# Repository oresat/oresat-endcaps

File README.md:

# "End Cap" PCBs for OreSat

These are the "end cap" PCBs that attach to the +Z and -Z ends of the satellites. Mostly these are to protect the end cards from "space", as well as to hold the magnetometers (two per end cap) as far as away from ferrous stuff as possible. It's also a good place for backup antennas, specifically patch antennas (S band and GPS L1).

## Features

- Cutouts for deployable antennas
- Double magnetometers.
- Single vertical 10mm tall 1.27 mm connector that plugs into the "end card" card.
    - On the End Cap:  Harwin M55-6001242R 12 pin female vertical connector 
    - On the End Card below: Harwin M55-7011242R 12 pin male vertical connector
- No available RF connectors.

## LICENSE

Copyright the Portland State Aerospace Society, 2024.

This source describes Open Hardware that is licensed under CERN-OHL-S v2, or any later version.

You may redistribute and modify this source and make products using it under the terms of the CERN-OHL-S v2 (https://ohwr.org/cern_ohl_s_v2.txt).

This source is distributed WITHOUT ANY EXPRESS OR IMPLIED WARRANTY, INCLUDING OF MERCHANTABILITY, SATISFACTORY QUALITY AND FITNESS FOR A PARTICULAR PURPOSE. Please see the CERN-OHL-S v2 for applicable conditions.

Source location: <https://github.com/oresat/>

As per CERN-OHL-S v2 section 4, should You produce hardware based on this source, You must where practicable maintain the Source Location visible on the external case of the Gizmo or other products you make using this source.

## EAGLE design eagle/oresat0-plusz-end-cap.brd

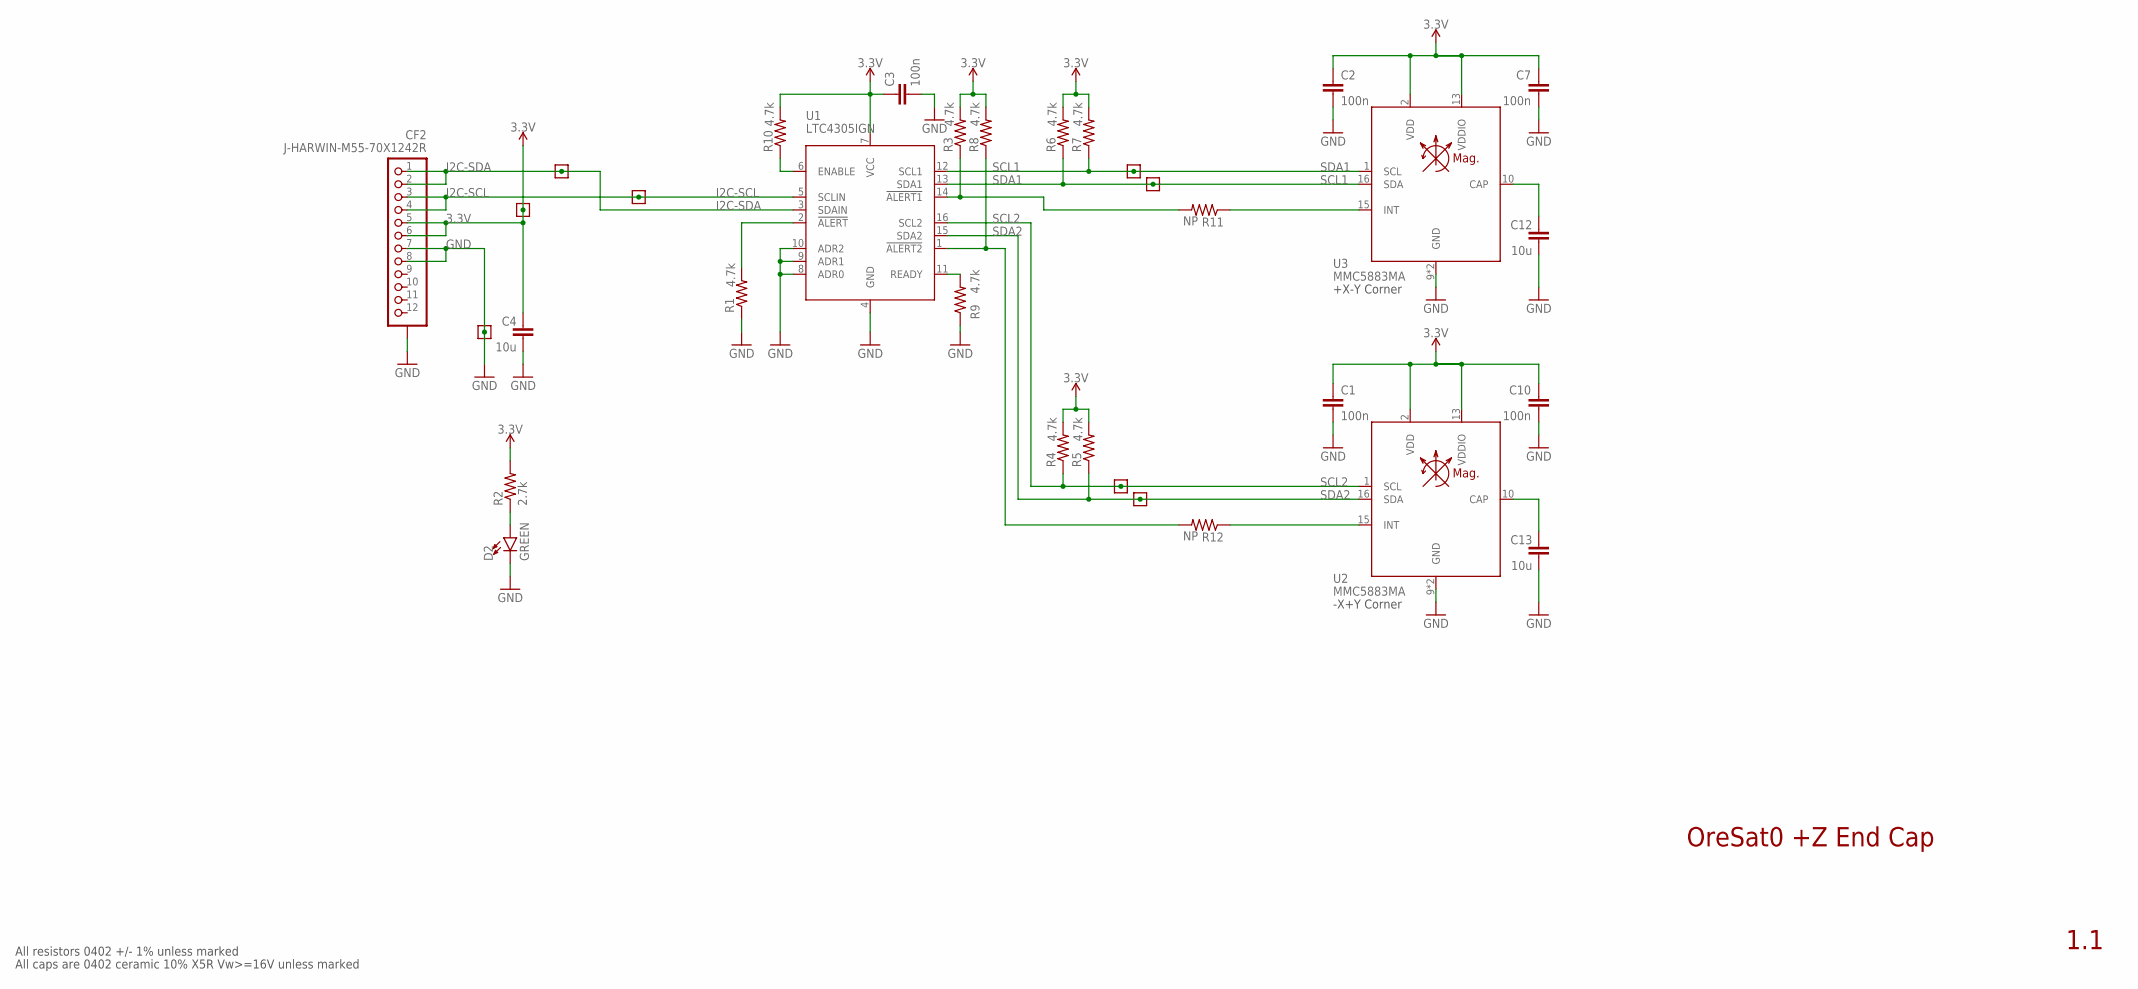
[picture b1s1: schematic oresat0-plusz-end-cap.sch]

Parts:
C1, C2, C3, C7, C10: 100n; .0603-B-NOSILK; MPN CL10B104KB8NNNL
C4, C12, C13: 10u; .0603-B-NOSILK; MPN GRM188D71A106KA73D
CF2: J-HARWIN-M55-70X1242R; HARWIN-M55-70X1242R; MPN M55-7011242R
D2: GREEN; LED-0603; MPN SML-E12M8WT86
R1, R3, R4, R5, R6, R7, R8, R9, R10: 4.7k; .0603-B-NOSILK; MPN CRGCQ0603F4K7
R2: 2.7k; .0603-B-NOSILK; MPN CRGCQ0603F2K7
R11, R12: NP; .0603-B-NOSILK
TP1, TP2, TP3, TP4, TP5, TP6, TP7, TP8: TEST-POINT-LARGE-SQUARE; 1X01
U1: LTC4305IGN; 16-SSOP; MPN LTC4305IGN#PBF
U2, U3: MMC5883MA; LGA-16(3X3); MPN MMC5883MA

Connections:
3.3V: C1.1, C2.1, C3.1, C4.1, C7.1, C10.1, CF2.5, CF2.6, R2.2, R3.2, R4.2, R5.2, R6.2, R7.2, R8.2, R10.2, TP7.1, U1.7 (VCC), U2.2 (VDD), U2.13 (VDDIO), U3.2 (VDD), U3.13 (VDDIO)
GND: C1.2, C2.2, C3.2, C4.2, C7.2, C10.2, C12.2, C13.2, CF2.7, CF2.8, CF2.P$1 (SHIELDS), CF2.P$2 (SHIELDS), CF2.P$3 (SHIELDS), CF2.P$4 (SHIELDS), D2.C, R1.1, R9.1, TP8.1, U1.4 (GND), U1.8 (ADR0), U1.9 (ADR1), U1.10 (ADR2), U2.9 (GND), U2.11 (GND), U3.9 (GND), U3.11 (GND)
I2C-SCL: CF2.3, CF2.4, TP3.1, U1.5 (SCLIN)
I2C-SDA: CF2.1, CF2.2, TP6.1, U1.3 (SDAIN)
unnamed: R9.2, U1.11 (READY)
unnamed: C12.1, U3.10 (CAP)
unnamed: R1.2, U1.2 (!ALERT)
unnamed: R3.1, R11.2, U1.14 (!ALERT1)
unnamed: C13.1, U2.10 (CAP)
unnamed: R8.1, R12.2, U1.1 (!ALERT2)
unnamed: R11.1, U3.15 (INT)
unnamed: R10.1, U1.6 (ENABLE)
unnamed: R12.1, U2.15 (INT)
unnamed: D2.A, R2.1
SCL1: R7.1, TP1.1, U1.12 (SCL1), U3.1 (SCL)
SCL2: R4.1, TP4.1, U1.16 (SCL2), U2.1 (SCL)
SDA1: R6.1, TP2.1, U1.13 (SDA1), U3.16 (SDA)
SDA2: R5.1, TP5.1, U1.15 (SDA2), U2.16 (SDA)

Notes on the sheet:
OreSat0 +Z End Cap
1.1
All resistors 0402 +/- 1% unless marked
All caps are 0402 ceramic 10% X5R Vw>=16V unless marked
-X+Y Corner
+X-Y Corner

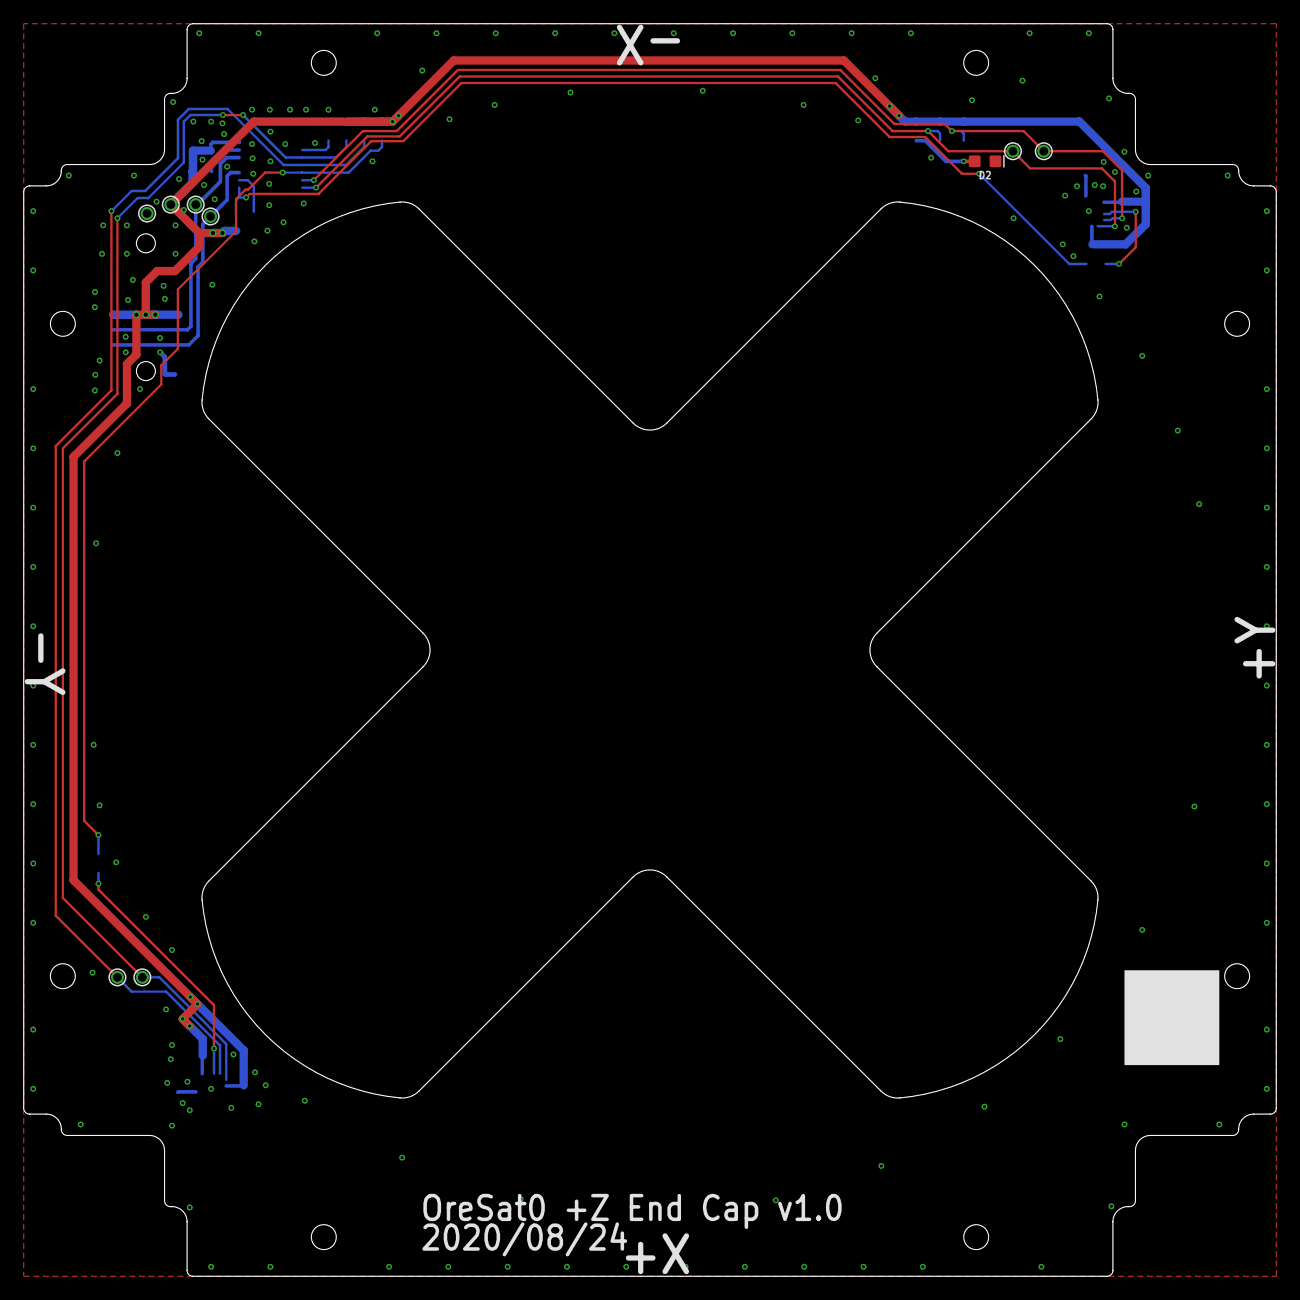
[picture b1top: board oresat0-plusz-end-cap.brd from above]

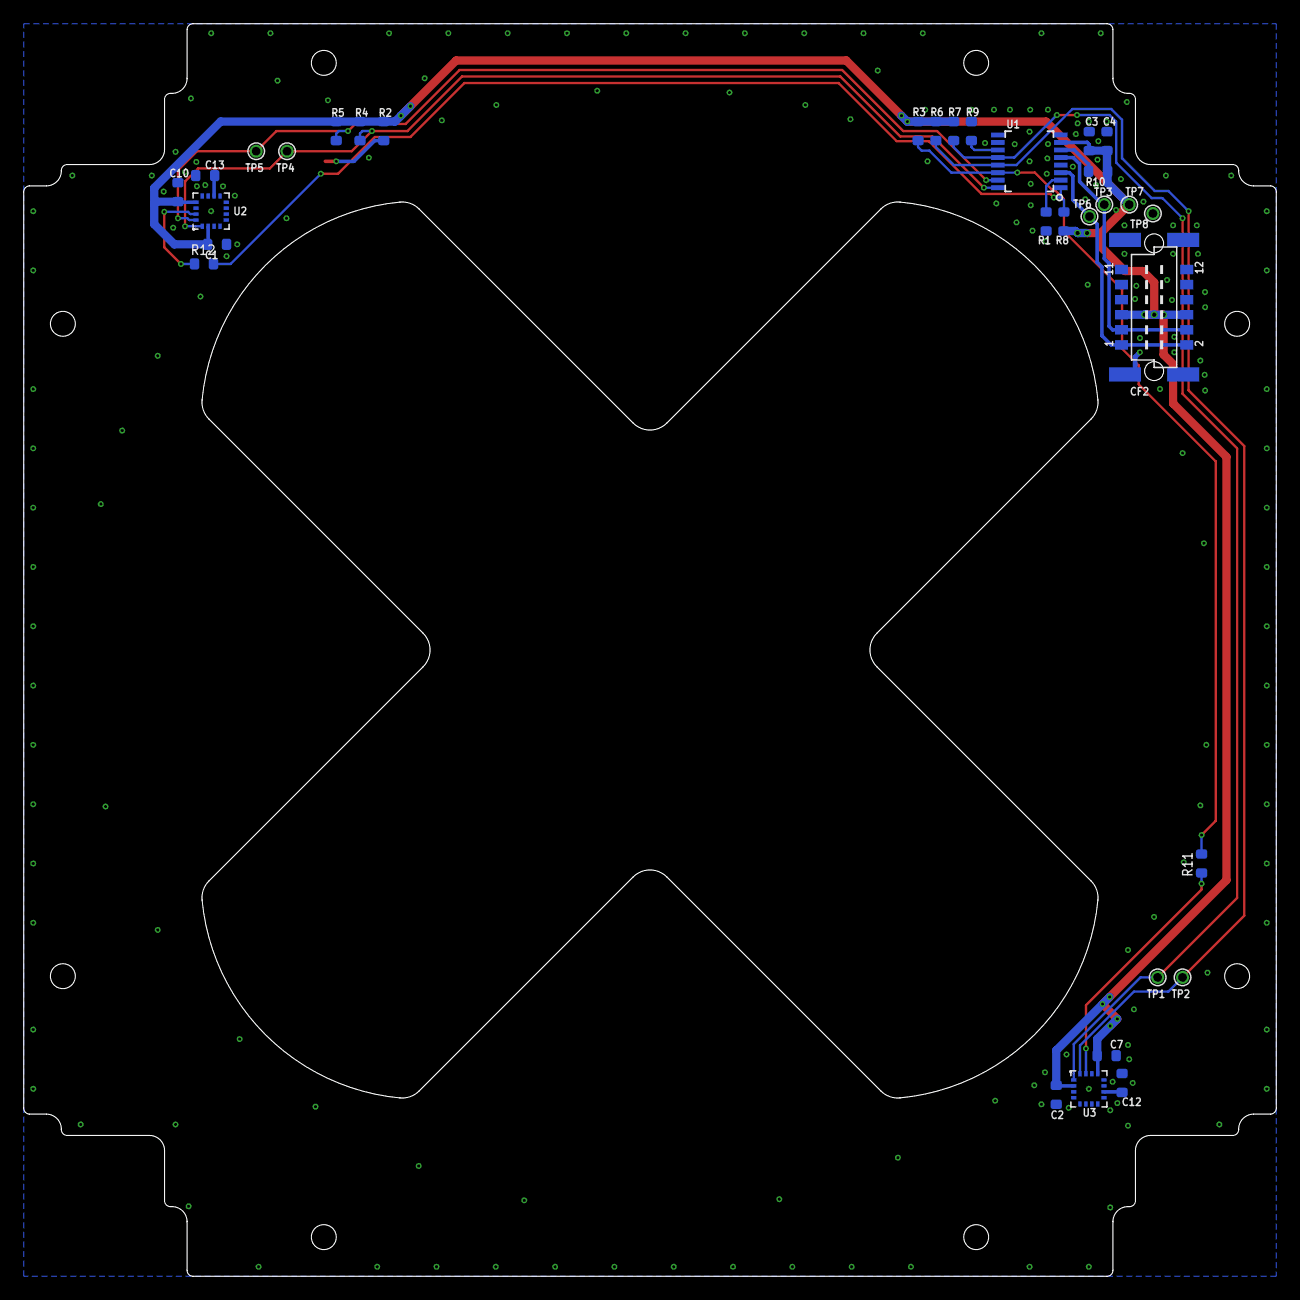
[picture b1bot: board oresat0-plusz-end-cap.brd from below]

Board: 2 copper layers, 105.6 x 105.6 mm, 33 parts (24 on the bottom side), 18 nets.

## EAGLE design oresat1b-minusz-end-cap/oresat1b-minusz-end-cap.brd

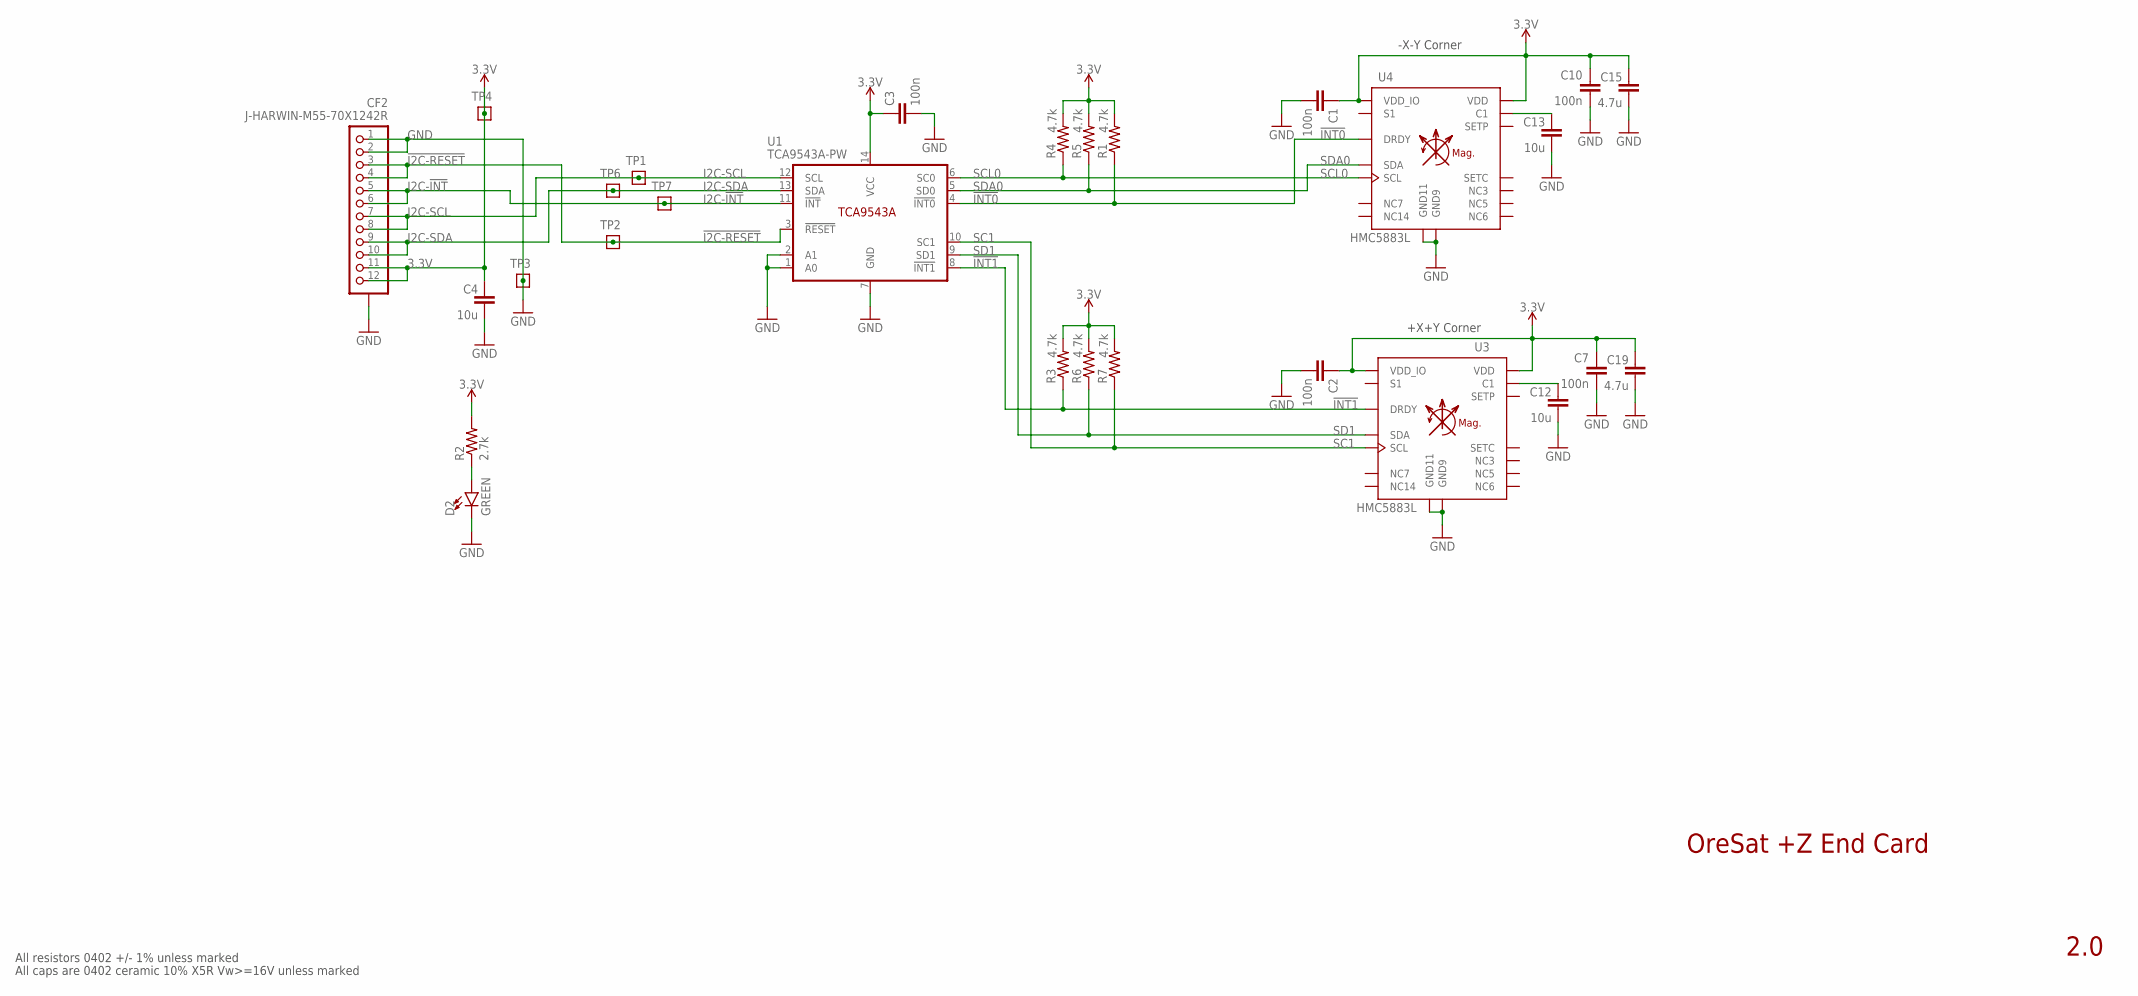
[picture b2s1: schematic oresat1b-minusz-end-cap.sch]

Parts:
C1, C2, C3, C7, C10: 100n; .0402-B-NOSILK; MPN CL05B104KO5NNNC
C4, C12, C13: 10u; .0603-B-NOSILK; MPN CL05B104KO5NNNC
C15, C19: 4.7u; .0603-B-NOSILK; MPN CL05B104KO5NNNC
CF2: J-HARWIN-M55-70X1242R; HARWIN-M55-70X1242R
D2: GREEN; LED-0603
R1, R3, R4, R5, R6, R7: 4.7k; .0402-B-NOSILK; MPN RC1005F6653CS
R2: 2.7k; .0402-B-NOSILK; MPN RC1005F6653CS
TP1, TP2, TP3, TP4, TP6, TP7: TEST-POINT; 2MM-TEST-POINT
U1: TCA9543A-PW; TSSOP14-0.65-5.4X4.4MM
U3, U4: HMC5883L; QLGA-16(3X3)

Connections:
3.3V: C1.1, C2.1, C3.1, C4.1, C7.1, C10.1, C15.1, C19.1, CF2.11, CF2.12, R1.2, R2.2, R3.2, R4.2, R5.2, R6.2, R7.2, TP4.1, U1.14 (VCC), U3.2 (VDD), U3.13 (VDD_IO), U4.2 (VDD), U4.13 (VDD_IO)
!I2C-RESET: CF2.3, CF2.4, TP2.1, U1.3 (!RESET)
!INT0: R1.1, U1.4 (!INT0), U4.15 (DRDY)
!INT1: R3.1, U1.8 (!INT1), U3.15 (DRDY)
GND: C1.2, C2.2, C3.2, C4.2, C7.2, C10.2, C12.2, C13.2, C15.2, C19.2, CF2.1, CF2.2, CF2.P$1 (SHIELDS), CF2.P$2 (SHIELDS), CF2.P$3 (SHIELDS), CF2.P$4 (SHIELDS), D2.C, TP3.1, U1.1 (A0), U1.2 (A1), U1.7 (GND), U3.9 (GND9), U3.11 (GND11), U4.9 (GND9), U4.11 (GND11)
I2C-!INT: CF2.5, CF2.6, TP7.1, U1.11 (!INT)
I2C-SCL: CF2.7, CF2.8, TP1.1, U1.12 (SCL)
I2C-SDA: CF2.9, CF2.10, TP6.1, U1.13 (SDA)
unnamed: C12.1, U3.10 (C1)
unnamed: C13.1, U4.10 (C1)
unnamed: D2.A, R2.1
SC1: R7.1, U1.10 (SC1), U3.1 (SCL)
SCL0: R4.1, U1.6 (SC0), U4.1 (SCL)
SD1: R6.1, U1.9 (SD1), U3.16 (SDA)
SDA0: R5.1, U1.5 (SD0), U4.16 (SDA)

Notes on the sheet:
OreSat +Z End Card
2.0
All resistors 0402 +/- 1% unless marked
All caps are 0402 ceramic 10% X5R Vw>=16V unless marked
-X-Y Corner
+X+Y Corner

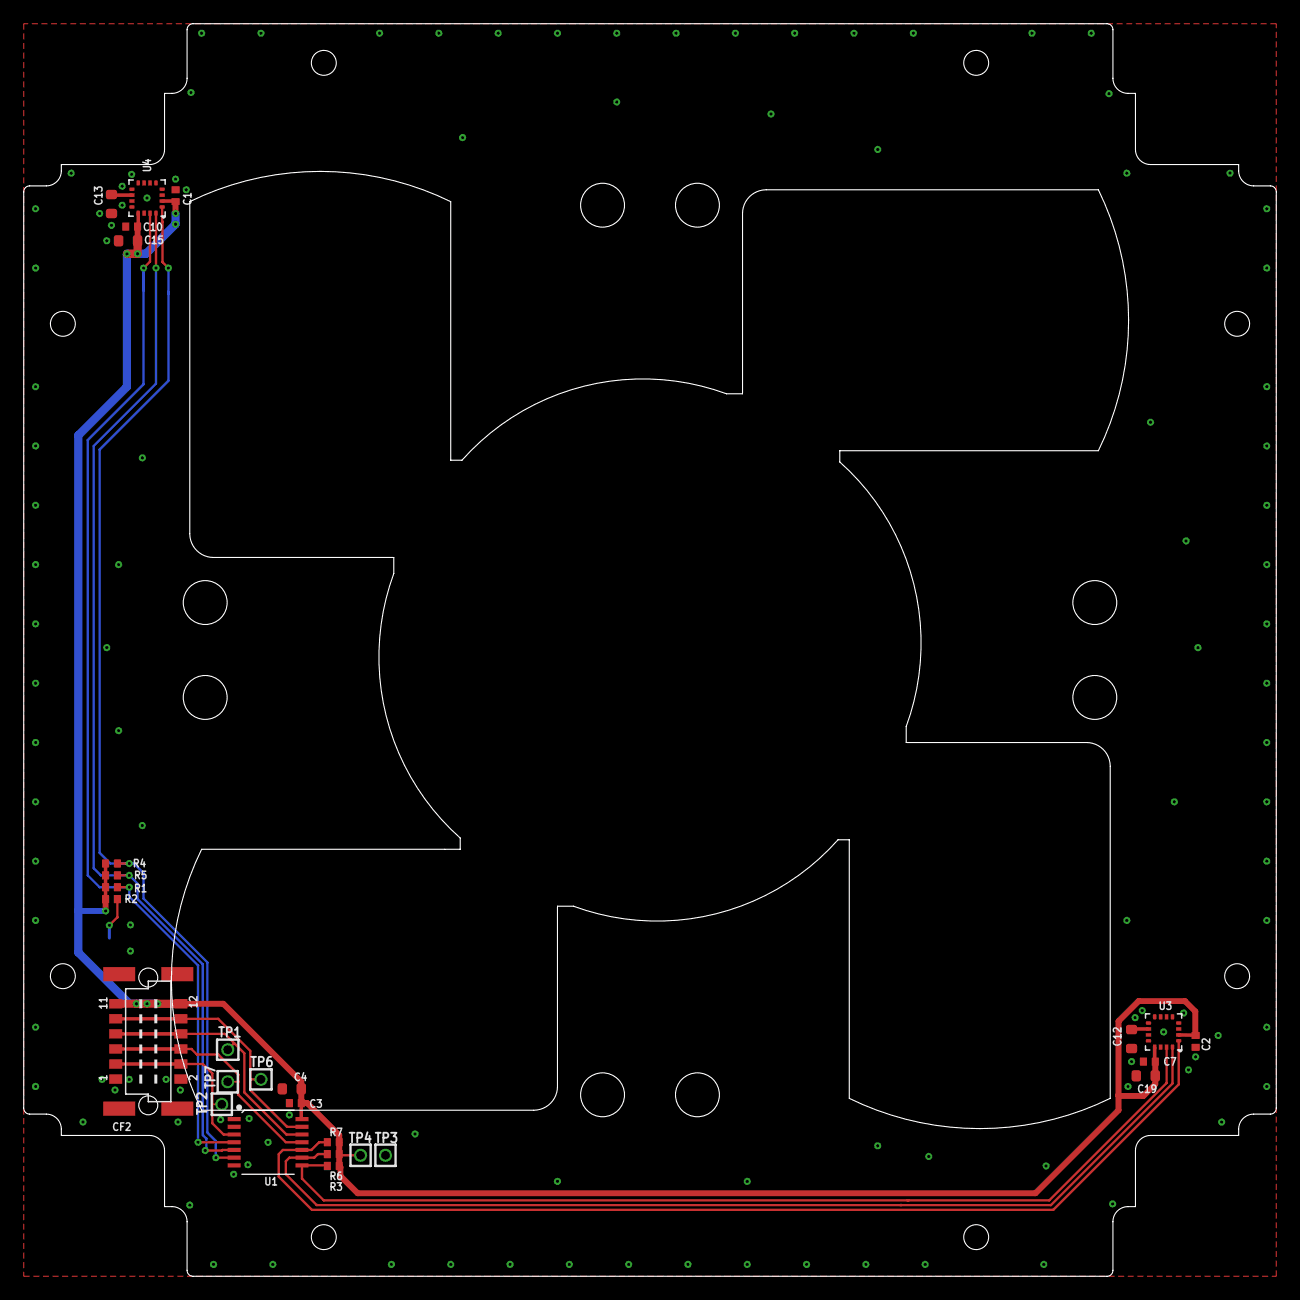
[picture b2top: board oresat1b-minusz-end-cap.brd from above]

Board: 2 copper layers, 105.6 x 105.6 mm, 28 parts (1 on the bottom side), 15 nets.

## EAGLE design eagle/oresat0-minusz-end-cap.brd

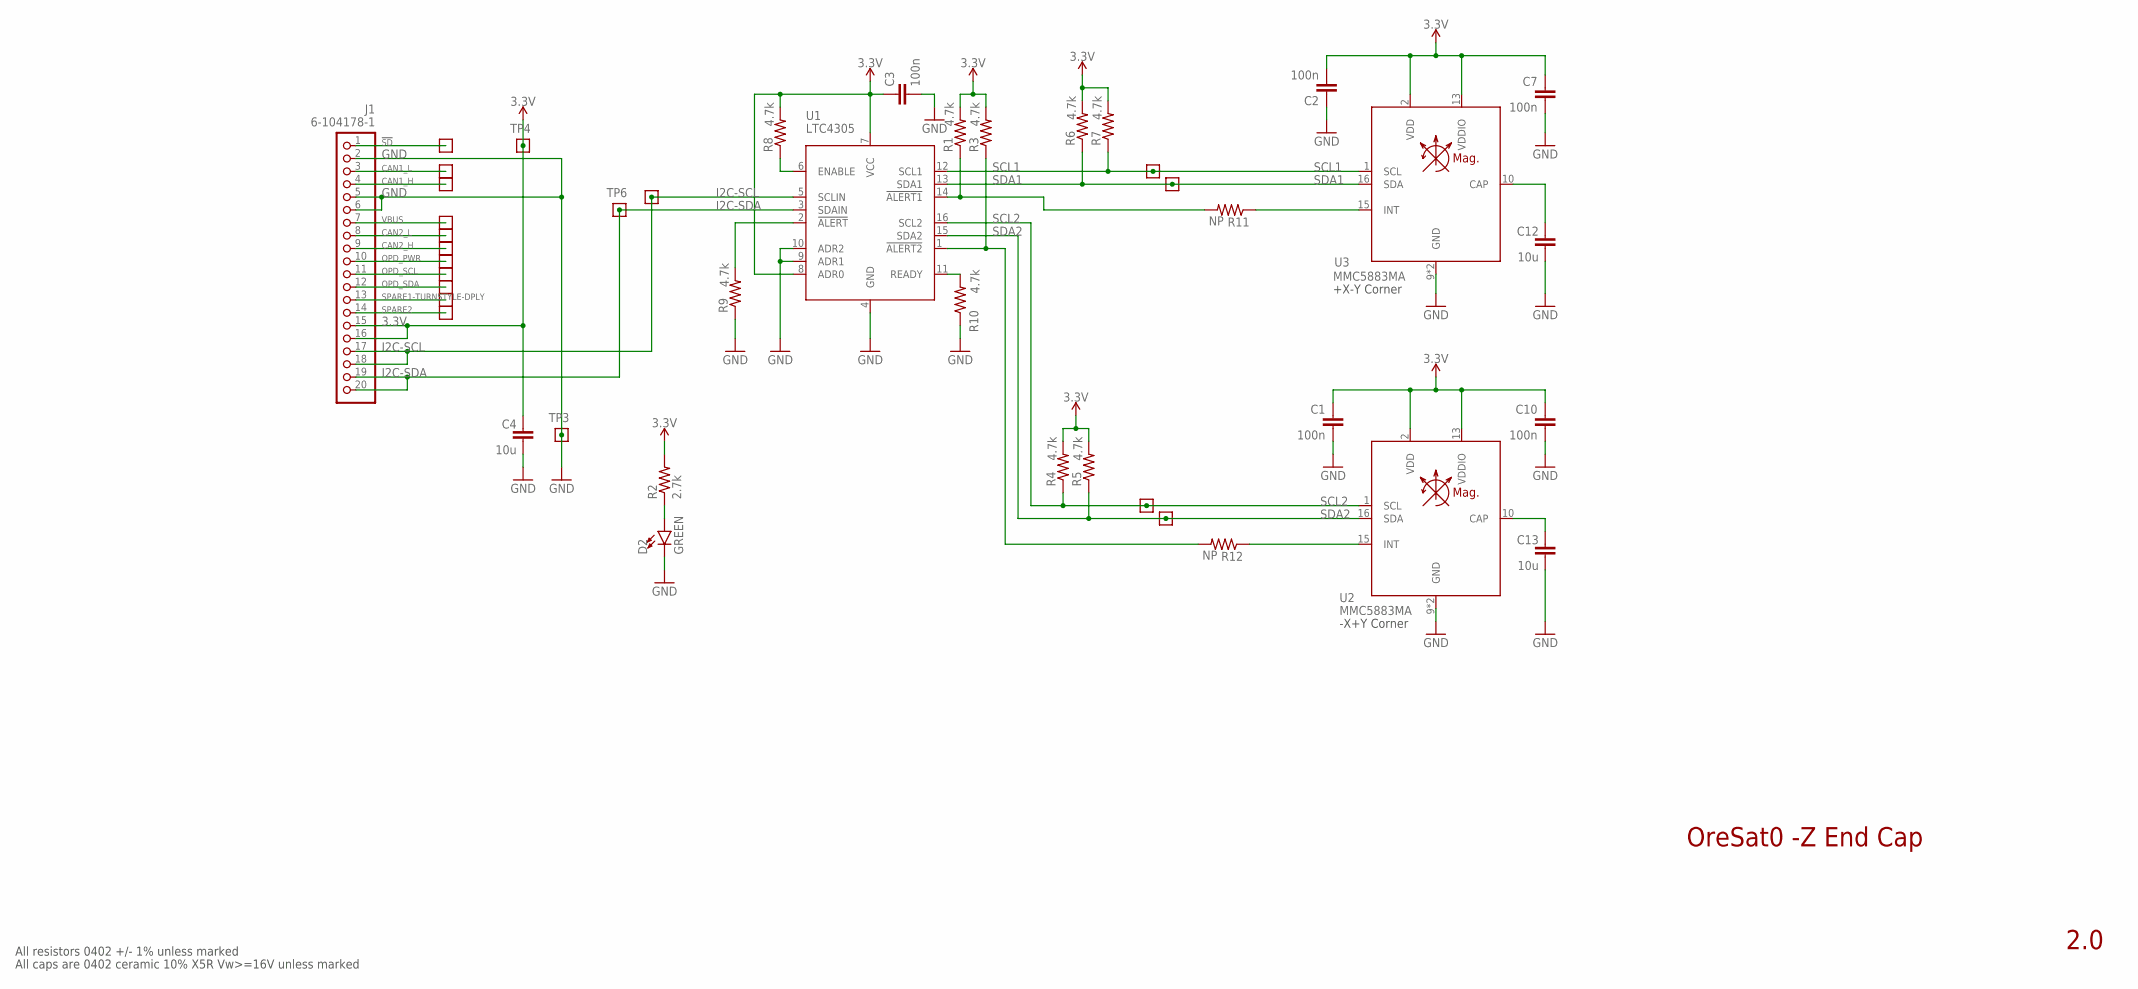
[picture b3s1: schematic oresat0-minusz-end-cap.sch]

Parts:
C1, C2, C3, C7, C10: 100n; .0603-B-NOSILK; MPN CL10B104KB8NNNL
C4, C12, C13: 10u; .0603-B-NOSILK; MPN GRM188D71A106KA73D
D2: GREEN; LED-0603; MPN SML-E12M8WT86
J1: 6-104178-1; MPN 6-104178-1
R1, R3, R4, R5, R6, R7, R8, R9, R10: 4.7k; .0603-B-NOSILK; MPN CRGCQ0603F4K7
R2: 2.7k; .0603-B-NOSILK; MPN CRGCQ0603F2K7
R11, R12: NP; .0603-B-NOSILK
TP1, TP2, TP3, TP4, TP5, TP6, TP7, TP8, TP9, TP10, TP11, TP12, TP13, TP14, TP15, TP16, TP17, TP18, TP19: TEST-POINT-LARGE-SQUARE; 1X01
U1: LTC4305; 16-SSOP; MPN LTC4305IGN#PBF
U2, U3: MMC5883MA; LGA-16(3X3); MPN MMC5883MA

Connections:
3.3V: C1.1, C2.2, C3.1, C4.1, C7.1, C10.1, J1.15, J1.16, R1.2, R2.2, R3.2, R4.2, R5.2, R6.2, R7.2, R8.2, TP4.1, U1.7 (VCC), U1.8 (ADR0), U2.2 (VDD), U2.13 (VDDIO), U3.2 (VDD), U3.13 (VDDIO)
!SD: J1.1, TP9.1
CAN1_H: J1.4, TP11.1
CAN1_L: J1.3, TP10.1
CAN2_H: J1.9, TP14.1
CAN2_L: J1.8, TP13.1
GND: C1.2, C2.1, C3.2, C4.2, C7.2, C10.2, C12.2, C13.2, D2.C, J1.2, J1.5, J1.6, R9.1, R10.1, TP3.1, U1.4 (GND), U1.9 (ADR1), U1.10 (ADR2), U2.9 (GND), U2.11 (GND), U3.9 (GND), U3.11 (GND)
I2C-SCL: J1.17, J1.18, TP1.1, U1.5 (SCLIN)
I2C-SDA: J1.19, J1.20, TP6.1, U1.3 (SDAIN)
unnamed: R8.1, U1.6 (ENABLE)
unnamed: C12.1, U3.10 (CAP)
unnamed: R1.1, R11.2, U1.14 (!ALERT1)
unnamed: R3.1, R12.2, U1.1 (!ALERT2)
unnamed: C13.1, U2.10 (CAP)
unnamed: R9.2, U1.2 (!ALERT)
unnamed: R10.2, U1.11 (READY)
unnamed: R11.1, U3.15 (INT)
unnamed: R12.1, U2.15 (INT)
unnamed: D2.A, R2.1
OPD_PWR: J1.10, TP15.1
OPD_SCL: J1.11, TP16.1
OPD_SDA: J1.12, TP17.1
SCL1: R7.1, TP2.1, U1.12 (SCL1), U3.1 (SCL)
SCL2: R4.1, TP7.1, U1.16 (SCL2), U2.1 (SCL)
SDA1: R6.1, TP5.1, U1.13 (SDA1), U3.16 (SDA)
SDA2: R5.1, TP8.1, U1.15 (SDA2), U2.16 (SDA)
SPARE1-TURNSTYLE-DPLY: J1.13, TP18.1
SPARE2: J1.14, TP19.1
VBUS: J1.7, TP12.1

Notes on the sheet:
OreSat0 -Z End Cap
2.0
All resistors 0402 +/- 1% unless marked
All caps are 0402 ceramic 10% X5R Vw>=16V unless marked
-X+Y Corner
+X-Y Corner

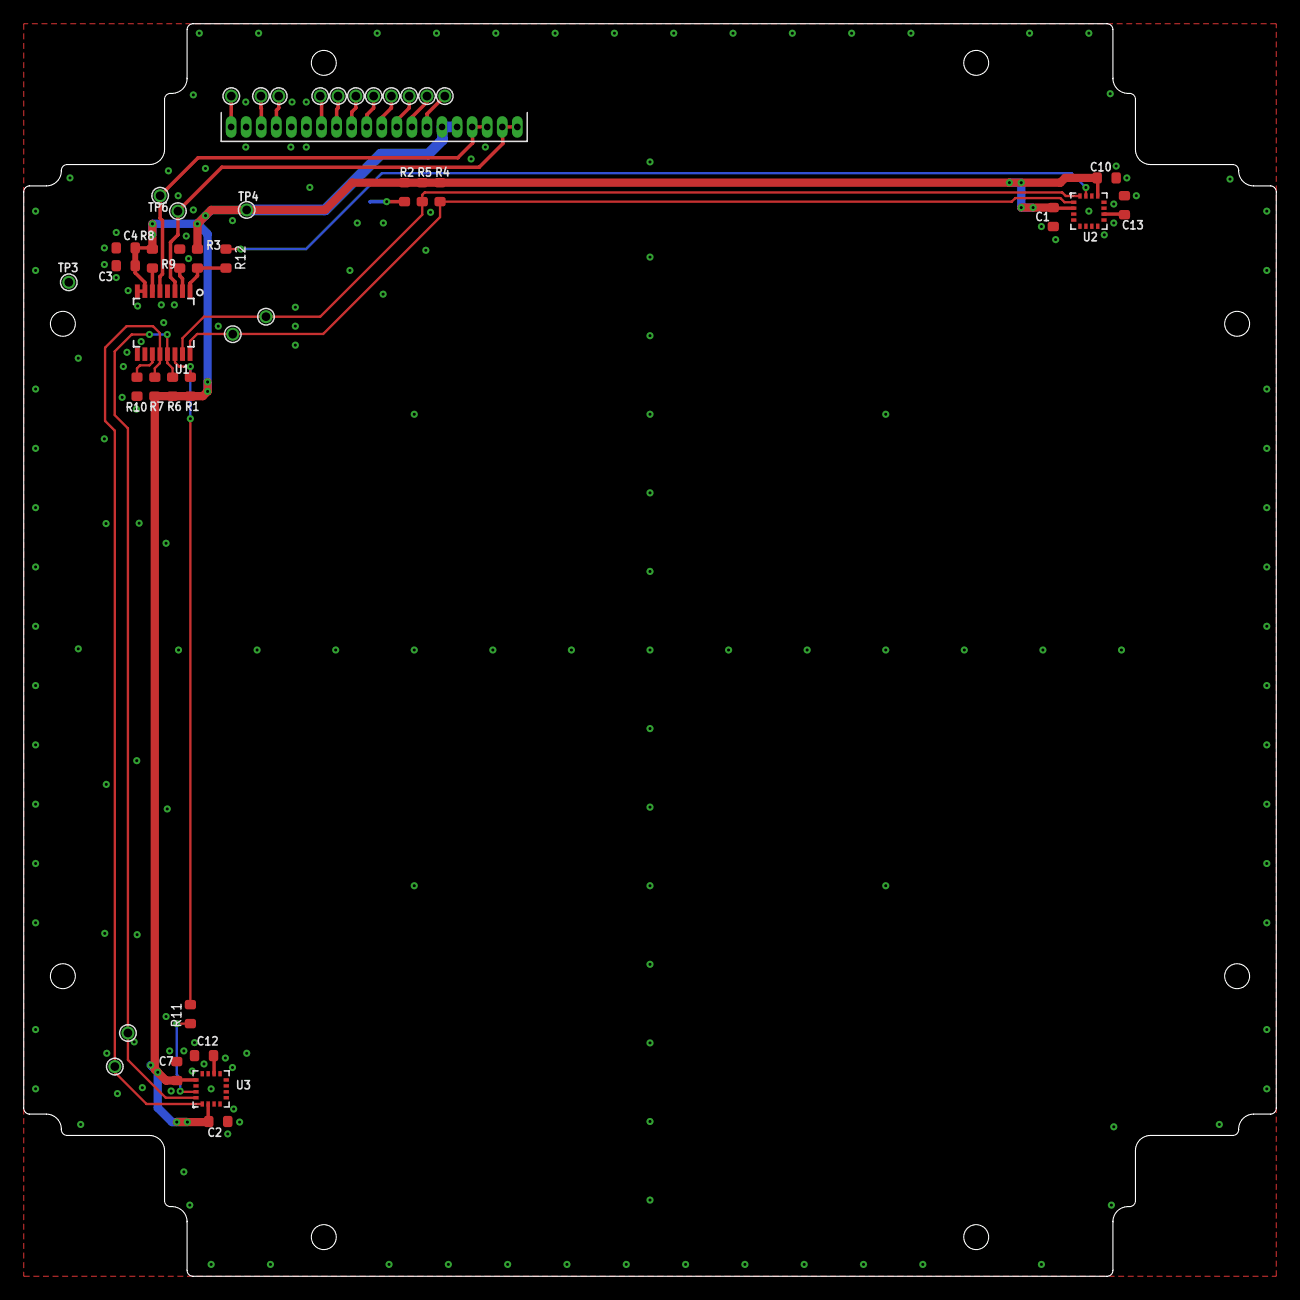
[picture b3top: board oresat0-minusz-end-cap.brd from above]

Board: 2 copper layers, 105.6 x 105.6 mm, 44 parts (1 on the bottom side), 29 nets.

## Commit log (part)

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2018-12-03 First try at a end card. Lots of stuff we don't need.
2018-12-03 Oh right, the bottom of the board.
2018-12-03 Updated version info on the board and readme, and added picture.
2018-12-03 Removed bad double title.
2018-12-19 Not done, but checking in anyway. Lots left to do, trying to figure out where things go.
2018-12-20 Removed SPS + uC blocks; only magnetometers remain on the end cap. Not great for future expandability, but moves uC to the end card where it's more useful.
2018-12-21 v1.0 done! All components on the inside to protect from The Spaces.
2018-12-21 Updated formatting.
2018-12-22 Updated outline based on new symmetrical end caps, decreased hole size but kept ground plane back.
2018-12-22 .. .and the -Z end cap. Again, just magnetometers.
2019-01-01 Added cutout for debug connector, update PNG.
2019-01-01 Added debug cutout to -Z end cap, and fixed README.
2019-02-25 Added updated keepouts for antennas; opened up helical opening.
2020-08-25 Added first version of OreSat0 end caps, though they are still not fully completed
2020-08-27 Added connector to backplane. Added NP resistors connecting magnetometer interrupts to i2c buffer alert inputs. Moved traces out of bstop area, and moved components away from the backplane. Changed b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
2020-08-27 Removed connector cutout from board outline. Increased restrict area for turnstile antenna. Changed some traces to the top layer to avoid the bstop area, and the new restrict area. Added NP resistors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
2020-08-28 v1.0 end caps for OreSat0!
2020-08-28 Moved SCL1 and SDA1 traces to avoid tstop area.
2020-08-29 Updated DXF and board outline. Also cleaned up tNames and Bplace layers around backplane connector.
2020-08-29 Added BOMs and updated attributes for OreSat0 + and - Z end caps.
2020-09-11 Fixed mysterious blank plus z BOM. Also added date and notes fields to minus z BOM.
2021-03-28 To begin redoing the +Z end cap board, I took the dimension layer from the 9-10-20 version of the board file and replaced it with the new DXF from Hayden Reinhold.
2021-03-28 I updated the dxf and dimension layers on the oresat 0 +Z end cap board. I also cleared all the DRC errors.
2021-04-09 New +Z end cap with larger cutout for turnstile.
    New -Z end cap with amazing artwork from Jennifer and thank yous.
2021-10-21 New pretty OreSat0 end cap, now with updated launch provider.
2021-11-09 Updated some of the back matter.
2021-11-10 bplace updates
    CRP & SP added to bplace layer
2022-07-25 Moved endcaps to KiCad
2022-07-25 Moved the oresat0 +z endcap to KiCad
2022-07-27 Moved OreSat0 -z to KiCad
2022-07-27 Added generic -z end cap
2023-02-06 Clean up directory structure to reflect per-satellite end caps
2023-02-12 Renamed to satellite name folders as per other repos
2023-02-17 Adds DXF of latest +Z end cap.
2023-02-17 Update oresat0.5 plusz end cap file names, and copied oresat0 plusz design, since old 0.5 design was ooooooold
2023-02-18 Updated oresat0.5 +Z board outline
2023-02-18 Adding DXF of OreSat0.5 -Z endcap
2023-02-18 Small fixes to oresat0.5 +Z end cap, and added new DXF to -Z cap. Also renamed minusz cap to oresat0.5-minusz
2023-02-19 Updated both oresat0.5 end caps. Fixed layout, and added patch antennas
2023-02-19 Updated both OreSat0.5 end caps and cleaned up errors
2023-02-19 OreSat0.5 end caps design review fixes
2023-02-21 Archiving Oresat0 +Z End Cap. Got rid of bad KiCAD import, made PDFs for future use.
2023-02-21 Archiving OreSat0 -Z end cap, with pretty PNGs and PDFs.
2023-02-21 Updated .gitignore for archive folder, updated readme, and killed old useless eagle file.
2023-02-21 Remove unused files; updated PCB with CAM settings.
2023-02-21 Removed unused files, added CAM settings to PCB file.
2023-02-21 Updated CAM settings in PCB
2023-02-21 Forgot silkscreen in CAM. Fixed.
2023-02-21 Added white silkscreen square for board number! Super critical! :)
2023-07-06 Adding DXF of OreSat0 -Z end cap.
2023-09-03 Updated end caps
2023-09-11 Updated magnetometer symbol
2023-09-11 Updated mounting holes
2023-09-15 OreSat0.5 -Z end cap. Updated to latest KiCAD, fixed lack of holes for lens holder, and removed solder mask from around screw heads.
2023-09-15 Oresat0.5 +Z End Cap. Still some weird library issues, but skipping for now.
2023-12-21 Upgrades OreSat0.5 +Z End Cap to v1.2 -- fits the new deployer, and cleans up a bunch of library issues.
2024-02-03 corrected board outline for OreSat 0.5 +z endcap
2024-02-29 Small changes to schematic, mostly comments.
2024-03-04 updated mmc5883 magnetometer to mmc5983 for both OreSat 0.5 +Z and -Z endcaps
2024-03-20 moved endcap harwin connectors on both +/-Z endcaps per move in Onshape
2024-03-21 Oresat 0.5 +z end cap v1.3 ready for ordering!
2024-03-21 OreSat 0.5 Endcaps (+Z v1.3 and -Z v1.2) ready for ordering, reviewed -Z endcap, made small library and neatness changes to +Z endcap
2024-04-08 Fixed issues 5 and 6 -- weird 4.7k values everywhere, missing libraries, and used no-place to indicate actual no place components.
2024-04-15 Added note on which MAG was which for firmware (PZ1 - MZ2).
2024-05-06 More information on end cap RF, including coax jumper for end cap.
2024-05-07 Updated BOM to include MFR/MPN/etc.
2024-05-08 Fixed BOM.
2024-12-12 Added KiCAD 8 import of OreSat0 +Z End Cap v1.1. Still needs lots of work to swich to KiCAD components, and get the schematic/layout synchronized.
2026-01-26 minus z endcap schematic & pcb w/ PNI rm3100 mag
    Beginning of rework w PNI rm3100
2026-01-31 RM 3100 board layout
    Round 1 - awaiting design review. Some issues with GND pads; DRC is clean, but looks weird. Debating if U1 needs to be further in the corner, therefore change its layout completely.
2026-02-01 Polishing the schematic and layout
    Cleaned up ERCs, lots of OCD polishing for no reason, added 3.3V zone, cleaned up 3.3V routing.
2026-02-01 Fix BOM and add 3D of antenna.
2026-02-05 Plus Z endcap - new dfx and rm3100 magnetometers.
    Routing complete. DRC warnings and errors about the antenna footprint. Labelled pads as unspecified (neither through hole or SMD) and still getting a warning. Other warnings about silkscreen being cl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
2026-02-06 New -Z DFX
    Added new DFX to edge.cuts and User.comments. Antenna footprint warning - juts out over cut.
2026-02-12 Added 3D models and fixed fab des
    3D models of antenna patch (-Z) and M55 connector & magIc2 chip on both boards.
2026-03-11 +Z End Cap ready for fab and assembly.
    Schematic: Made RM3100 symbol better, cleaned up schematic, added variable strings, DRC'd,
    added fiducials
    Layout: Added fiducials, cleaned up polygons, rerouted signals too close to the edge,
    Fixed the connector to the +Z End Card (it was wrong in so many ways), added all the
    3D models to things, fixed the Makefile to use STEP not VRML files, reset the footprint
    libraries Added the correct and latest DXF outline. Removed old DXF and old crusty
2026-03-11 Added note on patch antenna
2026-03-11 Added Oresat logo, updated PSAS logo!
2026-03-11 Tweak to logo files for DRC
2026-03-11 Better doc notes, including on U.FL to U.FL cabling
2026-04-10 Update OreSat1 +Z End Cap, but no new build, no substantial change from v1.0, just updated makefile, readme, and some library footprint updates.
2026-04-10 Add beginnings of the ESI -Z End Cap
2026-04-10 Added customized version of the +Z end cap for ESI
2026-04-11 New DFX & reposition GPS 7 magnetometers
2026-04-23 New DFX (bias left) & rerouted accordingly. Made pretty. Done?
2026-04-23 ESI -Z end cap, with build files, final answer
2026-04-23 update .gitignore for kicad 10

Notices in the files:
parts and their libraries:
SparkFun-LED: Licensing: Creative Commons ShareAlike 4.0 International - https://creativecommons.org/licenses/by-sa/4.0
